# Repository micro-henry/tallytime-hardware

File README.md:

<picture>
  <source media="(prefers-color-scheme: dark)" srcset="https://www.uhenry.com/assets/logo-tallytime-full-white.svg">
  
</picture>

# Tallytime (Hardware)

An open-source low-cost Tally & Timecode device, powered by RP2040 & LoRa

> [!NOTE]
> This project is WIP and is ongoing active development, expect breaking changes and modifications

## Features

- [ ]  LTC Timecode jam & generation
- [ ]  Wireless sync through LoRa modem
- [ ]  Direct syncing through raw bitstream
- [ ]  Microphone passthrough
- [ ]  Encoder & OLED screen
- [ ]  USB-C & battery charging

## Images

> Top
> 

> Bottom
> 

PCB renders generated with a modified version (custom fonts) of [linalinn/kicad-render](https://github.com/linalinn/kicad-render)

## Authors

- [@Kelvin-Ziqi-Zhao](https://www.github.com/Kelvin-Ziqi-Zhao)
- [@Treeezheng](https://www.github.com/Treeezheng)
- [@Arom1a](https://www.github.com/Arom1a)
- [@plushugh](https://www.github.com/plushugh)

## License

[CERN-OHL-S-2.0](https://ohwr.org/cern_ohl_s_v2.txt)

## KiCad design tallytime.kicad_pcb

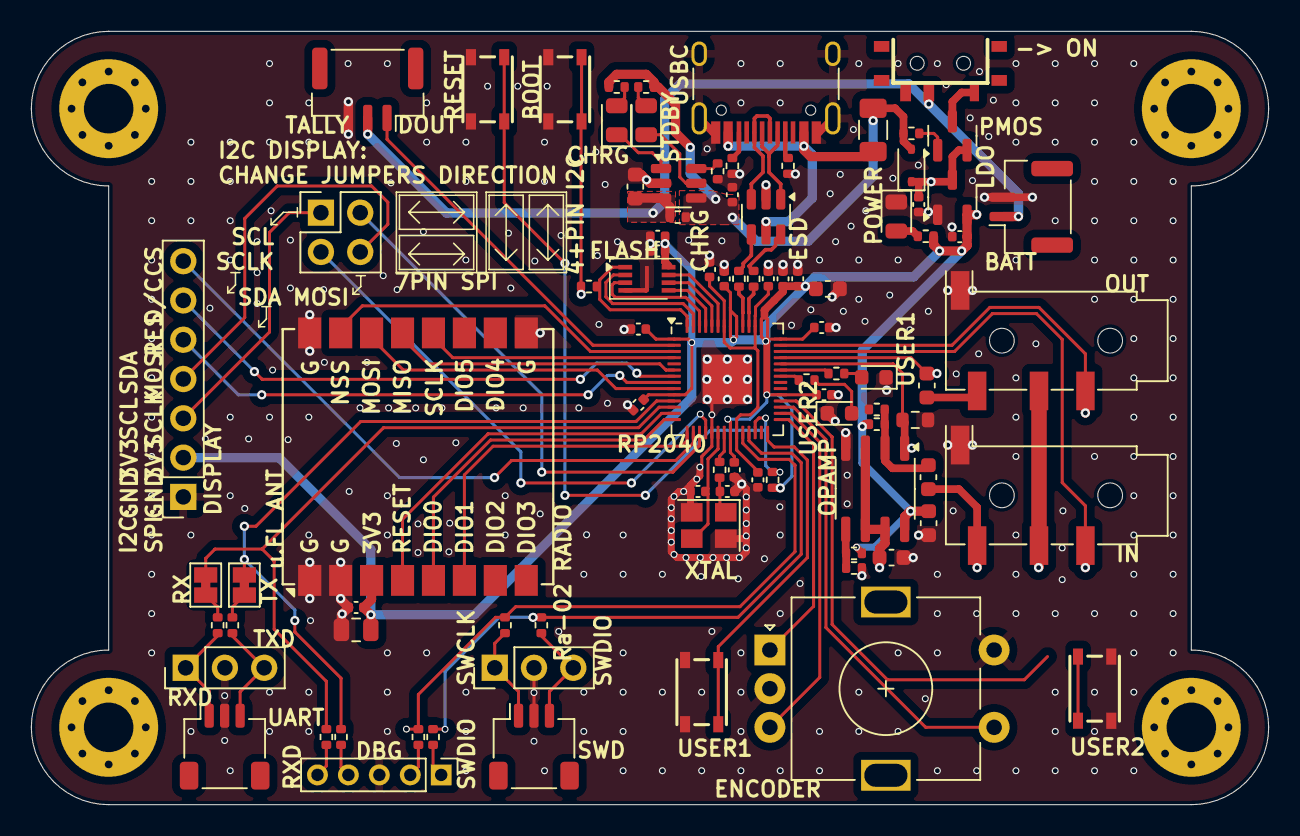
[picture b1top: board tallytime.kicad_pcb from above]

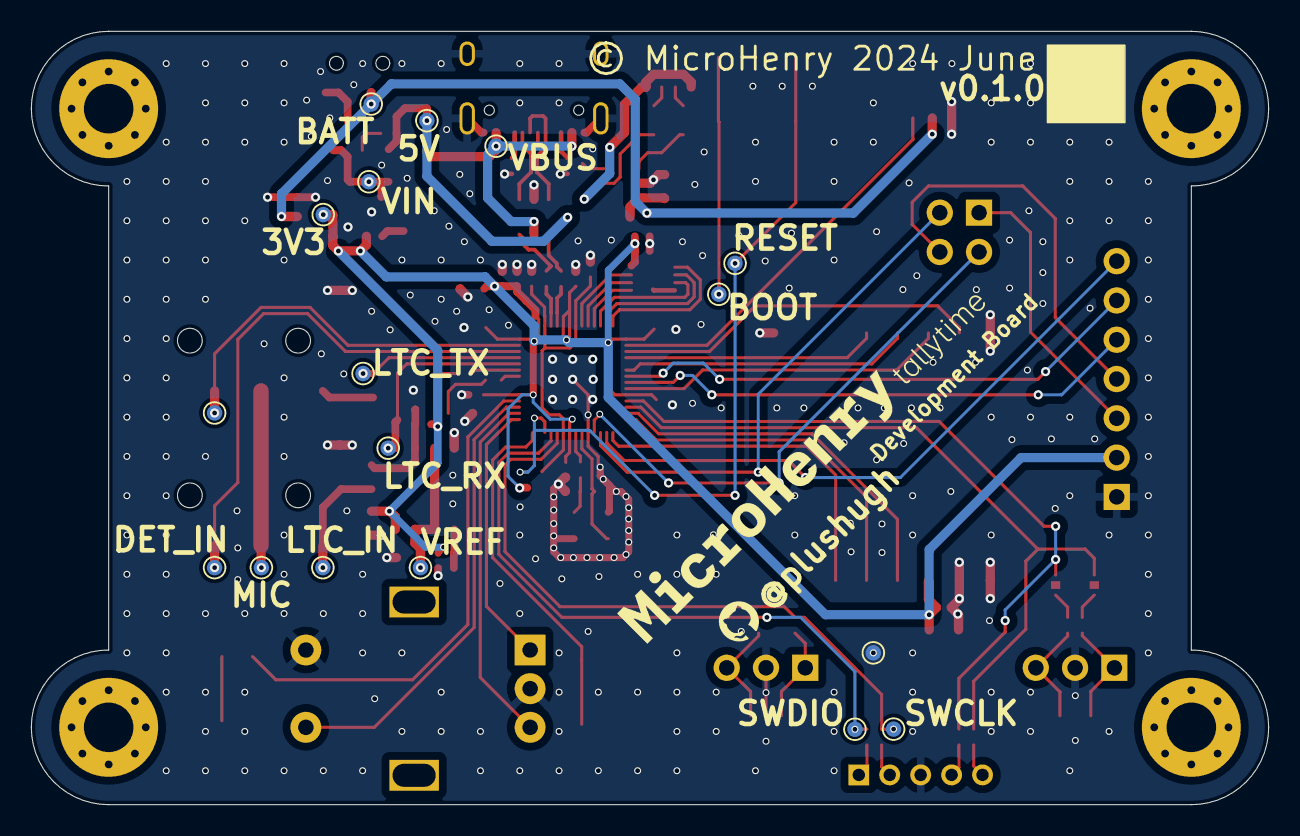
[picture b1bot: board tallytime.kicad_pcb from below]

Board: 4 copper layers, 80.0 x 50.0 mm, 111 parts (17 on the bottom side), 82 nets.

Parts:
C1, C2, C3, C4, C5, C6, C7, C8, C9, C14, C18: 100n; C_0402_1005Metric
C10, C19, C20, C21, C22, C25: 10u; C_0603_1608Metric
C11, C12, C23, C24, C26: 1u; C_0402_1005Metric
C13: 2.2u; C_0402_1005Metric
C15, C16: 33p; C_0402_1005Metric
C17: 22u; C_0805_2012Metric
D1: USERLED1; LED_0603_1608Metric
D2: USERLED2; LED_0603_1608Metric
D3: 1N5819WS; D_SOD-323
D4, D6: RED; LED_0805_2012Metric
D5: GREEN; LED_0805_2012Metric
F1: 1.5A; Fuse_1206_3216Metric
H1, H2, H3, H4: MountingHole_Pad; MountingHole_3.2mm_M3_Pad_Via
J1: USB_C_Receptacle_USB2.0_16P; USB_C_Receptacle_HRO_TYPE-C-31-M-12
J2: SWD; PinHeader_1x03_P2.54mm_Vertical
J3, J6: SM03B-SRSS-TB; JST_SH_SM03B-SRSS-TB_1x03-1MP_P1.00mm_Horizontal
J4: 5PIN HOLES; PinHeader_1x05_P2.00mm_Vertical
J5: UART; PinHeader_1x03_P2.54mm_Vertical
J7, J8: TRRS Out; Jack_3.5mm_KoreanHropartsElec_PJ-320D-4A_Horizontal
J9: Conn_02x02_Counter_Clockwise; PinHeader_2x02_P2.54mm_Vertical
J10: OLED DISPLAY; PinSocket_1x07_P2.54mm_Vertical
J12: BATT; JST_GH_SM02B-GHS-TB_1x02-1MP_P1.25mm_Horizontal
J13: TALLY LIGHT; JST_GH_SM03B-GHS-TB_1x03-1MP_P1.25mm_Horizontal
JP1: UART_RX; SolderJumper-2_P1.3mm_Bridged_Pad1.0x1.5mm
JP2: UART_TX; SolderJumper-2_P1.3mm_Bridged_Pad1.0x1.5mm
Q1: AO3401A; SOT-23
R1, R2, R3: 1k; R_0402_1005Metric
R4, R5, R16, R17, R23, R24, R25, R26, R27: 5k1; R_0402_1005Metric
R6, R7: 22; R_0402_1005Metric
R8, R9, R10, R11, R12, R13, R14, R15: 100; R_0402_1005Metric
R18, R19, R20, R22: 10k; R_0402_1005Metric
R21: 150k; R_0603_1608Metric
R28: 2k; R_0402_1005Metric
SW1, SW2, SW4, SW5: SKRPACE010
SW3: EC11; RotaryEncoder_Alps_EC11E-Switch_Vertical_H20mm
SW6: SW_SPDT; SW-SMD_3P-P1.50_L2.7-W6.6
TP1: VBUS; TestPoint_Pad_D1.0mm
TP2: SWCLK; TestPoint_Pad_D1.0mm
TP3: SWDIO; TestPoint_Pad_D1.0mm
TP4: BOOT; TestPoint_Pad_D1.0mm
TP5: RESET; TestPoint_Pad_D1.0mm
TP6: VREF; TestPoint_Pad_D1.0mm
TP7: LTC_RX; TestPoint_Pad_D1.0mm
TP8: LTC_TX; TestPoint_Pad_D1.0mm
TP9: LTC_IN; TestPoint_Pad_D1.0mm
TP10: MIC; TestPoint_Pad_D1.0mm
TP11: DET_IN; TestPoint_Pad_D1.0mm
TP12: DET_OUT; TestPoint_Pad_D1.0mm
TP13: BATT; TestPoint_Pad_D1.0mm
TP14: VIN; TestPoint_Pad_D1.0mm
TP15: 3V3; TestPoint_Pad_D1.0mm
TP16: 5V; TestPoint_Pad_D1.0mm
TP17: GND; TestPoint_Pad_D1.0mm
U1: W25Q16JVUXIQ; SON50P300X200X60-9N
U2: RP2040; QFN-56-1EP_7x7mm_P0.4mm_EP3.2x3.2mm
U3: USBLC6-2SC6; SOT-23-6
U4: Ai-Thinker-Ra-02; Ai-Thinker-Ra-01-LoRa
U5: LM358; SOP-8_3.9x4.9mm_P1.27mm
U6: XC6206P332MR; SOT-23-3
U7: TP4057; SOT-23-6
Y1: 12MHz +-10ppm 20pF; Crystal_SMD_3225-4Pin_3.2x2.5mm

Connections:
+1V1: C1.1, C2.1, C11.1, U2.23 (DVDD), U2.45 (VREG_VOUT), U2.50 (DVDD)
+3V3: C3.1, C4.1, C5.1, C6.1, C7.1, C8.1, C9.1, C10.1, C12.1, C13.1, C14.1, C17.1, C18.1, C19.1, C24.1, J10.2, R1.1, R18.1, R20.1, R24.1, TP15.1, U1.8 (VCC), U2.1 (IOVDD), U2.10 (IOVDD), U2.22 (IOVDD), U2.33 (IOVDD), U2.42 (IOVDD), U2.43 (ADC_AVDD), U2.44 (VREG_IN), U2.48 (USB_VDD), U2.49 (IOVDD), U4.3 (VDD), U5.8 (V+), U6.2 (VO)
+5V: C26.1, D3.2 (A), F1.2, R23.1, R25.1, R26.1, R27.1, TP16.1, U7.4 (VCC)
+BATT: C25.1, J12.1, J13.2, R27.2, SW6.2 (B), TP13.1, U7.3 (BAT)
+VIN: C23.1, D3.1 (K), Q1.2 (S), TP14.1, U6.3 (VI)
/Debug/3PIN_SWD_SWCLK: J2.1, J3.1, R9.1
/Debug/3PIN_SWD_SWDIO: J2.3, J3.3, R11.1
/Debug/3PIN_UART_RX: J5.1, J6.1, R14.1
/Debug/3PIN_UART_TX: J5.3, J6.3, R15.1
/Debug/5PIN_SWD_SWCLK: J4.2, R10.1
/Debug/5PIN_SWD_SWDIO: J4.1, R8.1
/Debug/5PIN_UART_RX: J4.5, R13.1
/Debug/5PIN_UART_TX: J4.4, R12.1
/Debug/ENCODER_A: SW3.A, U2.29 (GPIO18)
/Debug/ENCODER_B: SW3.B, U2.30 (GPIO19)
/Debug/ENCODER_SW: SW3.S1, U2.31 (GPIO20)
/Debug/JMP_UART_RX: JP1.2 (B), R14.2
/Debug/JMP_UART_TX: JP2.2 (B), R15.2
/Debug/SWCLK: R9.2, R10.2, TP2.1, U2.24 (SWCLK)
/Debug/SWDIO: R8.2, R11.2, TP3.1, U2.25 (SWD)
/Debug/TALLY: J13.1, U2.2 (GPIO0)
/Debug/UART_RX: JP1.1 (A), R13.2, U2.12 (GPIO9)
/Debug/UART_TX: JP2.1 (A), R12.2, U2.11 (GPIO8)
/Debug/USERLED1: R16.1, U2.37 (GPIO25)
/Debug/USERLED1_K: D1.2 (A), R16.2
/Debug/USERLED2: R17.1, U2.36 (GPIO24)
/Debug/USERLED2_K: D2.2 (A), R17.2
/Debug/USERSW1: SW2.1, SW2.3, U2.28 (GPIO17)
/Debug/USERSW2: SW5.1, SW5.3, U2.32 (GPIO21)
/Debug/~BOOT: R2.1, SW1.1, SW1.3, TP4.1
/Debug/~RESET: R1.2, SW4.1, SW4.3, TP5.1, U2.26 (RUN)
/Display/CS: J10.7, U2.16 (GPIO13)
/Display/D/C: J10.6, U2.7 (GPIO5)
/Display/MOSI_SDA: J9.4, J10.4
/Display/RES: J10.5, U2.8 (GPIO6)
/Display/SCLK_SCL: J9.1, J10.3
/Display/SCL_MOSI: J9.3, U2.18 (GPIO15)
/Display/SDA_SCLK: J9.2, U2.17 (GPIO14)
/MCU/GPIO1: U2.3 (GPIO1), U4.15 (~NSS)
/MCU/GPIO2: U2.4 (GPIO2), U4.12 (SCK)
/MCU/GPIO4: U2.6 (GPIO4), U4.13 (MISO)
/MCU/GPIO7: U2.9 (GPIO7), U4.14 (MOSI)
/MCU/GPIO10: U2.13 (GPIO10), U4.4 (~RESET)
/MCU/GPIO11: U2.14 (GPIO11), U4.5 (DIO0)
/MCU/GPIO12: U2.15 (GPIO12), U4.6 (DIO1)
/MCU/GPIO26_ADC0: R21.1, TP7.1, U2.38 (GPIO26_ADC0), U5.1
/MCU/GPIO27_ADC1: C22.1, TP8.1, U2.39 (GPIO27_ADC1)
/MCU/GPIO28_ADC2: J7.R2, TP11.1, U2.40 (GPIO28_ADC2)
/MCU/GPIO29_ADC3: J8.R2, TP12.1, U2.41 (GPIO29_ADC3)
/MCU/QSPI_SCLK: U1.6 (CLK), U2.52 (QSPI_SCLK)
/MCU/QSPI_SD0: U1.5 (DI_(IO0)), U2.53 (QSPI_SD0)
/MCU/QSPI_SD1: U1.2 (DO_(IO1)), U2.55 (QSPI_SD1)
/MCU/QSPI_SD2: U1.3 (~WP_(IO2)), U2.54 (QSPI_SD2)
/MCU/QSPI_SD3: U1.7 (~HOLD_OR_RESET_(IO3)), U2.51 (QSPI_SD3)
/MCU/QSPI_SS: R2.2, U1.1 (~CS), U2.56 (QSPI_SS)
/MCU/USB_D+: R7.2, U2.47 (USB_DP)
/MCU/USB_D-: R6.2, U2.46 (USB_DM)
/MCU/XIN: C15.2, U2.20 (XIN), Y1.3
/MCU/XOUT: R3.2, U2.21 (XOUT)
/MCU/XTAL_XOUT: C16.2, R3.1, Y1.1
/Power/BATT_SW: Q1.3 (D), SW6.1 (A)
/Power/MOS_BIAS: Q1.1 (G), R23.2
/Power/POWER_LED_K: D4.2 (A), R24.2
/Timecode/LTC_IN: C21.1, J7.T, TP9.1
/Timecode/LTC_OUT: C22.2, J8.T
/Timecode/MIC_PASSTHROUGH: J7.R1, J8.R1, TP10.1
/Timecode/OPAMP_A_N: C21.2, R20.2, R22.1, U5.2 (-)
/Timecode/OPAMP_B_P: R18.2, R19.1, U5.5 (+)
/Timecode/VREF: C20.1, TP6.1, U5.3 (+), U5.6 (-), U5.7
/USB/USBD+: J1.A6 (D+), J1.B6 (D+), U3.3 (I/O2)
/USB/USBD-: J1.A7 (D-), J1.B7 (D-), U3.1 (I/O1)
/USB/USBESD+: R7.1, U3.4 (I/O2)
/USB/USBESD-: R6.1, U3.6 (I/O1)
/USB/USB_CC1: J1.A5 (CC1), R4.1
/USB/USB_CC2: J1.B5 (CC2), R5.1
GND: C1.2, C2.2, C3.2, C4.2, C5.2, C6.2, C7.2, C8.2, C9.2, C10.2, C11.2, C12.2, C13.2, C14.2, C15.1, C16.1, C17.2, C18.2, C19.2, C20.2, C23.2, C24.2, C25.2, C26.2, D1.1 (K), D2.1 (K), D4.1 (K), J1.A1 (GND), J1.A12 (GND), J1.B1 (GND), J1.B12 (GND), J1.S1 (SHIELD), J2.2, J3.2, J4.3, J5.2, J6.2, J7.S, J8.S, J10.1, J12.2, J13.3, R4.2, R5.2, R19.2, R21.2, R22.2, R28.2, SW1.2, SW1.4, SW2.2, SW2.4, SW3.C, SW3.S2, SW4.2, SW4.4, SW5.2, SW5.4, TP17.1, U1.4 (GND), U1.9 (EP), U2.19 (TESTEN), U2.57 (GND), U3.2 (GND), U4.1 (GND), U4.2 (GND), U4.9 (GND), U4.16 (GND), U5.4 (V-), U6.1 (GND), U7.2 (GND), Y1.2, Y1.4
unnamed: D5.2 (A), R25.2
unnamed: D5.1 (K), U7.5 (~STDBY)
unnamed: D6.2 (A), R26.2
unnamed: D6.1 (K), U7.1 (~CHRG)
unnamed: R28.1, U7.6 (PROG)
VBUS: F1.1, J1.A4 (VBUS), J1.A9 (VBUS), J1.B4 (VBUS), J1.B9 (VBUS), TP1.1, U3.5 (VBUS)

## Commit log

2023-09-20 (feat): Add KiCad Symbol and Footprint Libraries
2023-09-21 (init): create dev_board KiCad project
2023-09-22 feat: add MCU to dev board
2023-09-22 docs: add official rp2040 hardware design guide to ref
2023-09-22 docs: add minimal design example to ref
2023-09-22 docs: add rp2040 datasheet to ref
2023-09-23 docs: add guide paper to ref
2023-09-23 Update .gitignore: add ignore condition
2023-09-23 feat: add power net
    add decoupling capacitor to MCU
    build 1v1 and 3v3 power bus
2023-09-24 feat: complete mcu basic circuit design
2023-09-27 Delete dev_board_v0.1.x/ref directory
    files in ref directory will be transfer to google drive
2023-09-27 Create README for dev board directory
2024-04-08 init: add files via upload
2024-04-08 actions: Create pcb_image.yml
2024-04-08 actions(pcb_image): include fonts
2024-04-08 actions(pcb_image): update pages actions
2024-04-08 actions(pcb_image): fix inter font URL
2024-04-08 actions(pcb_image): use fork of renderer with fonts
2024-04-08 actions(pcb_image): fix deploy action version
2024-04-08 feat: create README.md
2024-04-08 feat: create LICENSE
2024-04-08 feat(readme): update README.md
    fix license title, add render credit
2024-04-12 feat: optimizations
2024-04-13 feat: ESD optimizations
2024-07-03 v0.1.0

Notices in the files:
tallytime.kicad_pcb:
© MicroHenry 2024 June
